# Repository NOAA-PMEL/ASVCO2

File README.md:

# ASVCO2
Open Source Repository for the Autonomous Surface Vehicle CO2 (ASVCO2) gen2 system's firmware and electronics hardware.

## Attribution
You agree to acknowledge NOAA-PMEL and UW on splash pages, and in publications, for products developed with this software.

## UW License
*Refer to the LICENSE file.*

## NOAA Legal Disclaimers
*NOAA does not intend to patent this work worldwide. It may be used freely, but NOAA does not warrant its fitness for any use.*

*As a work of the United States Government, the associated schematics and software are in the public domain within the United States. Additionally, NOAA waives any potential copyright and related rights in the associated schematics and software worldwide.*

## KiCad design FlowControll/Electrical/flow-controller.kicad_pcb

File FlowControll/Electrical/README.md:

# EDD-flow-controller-kicad
KiCad port of ASVCO2 Flow Control board

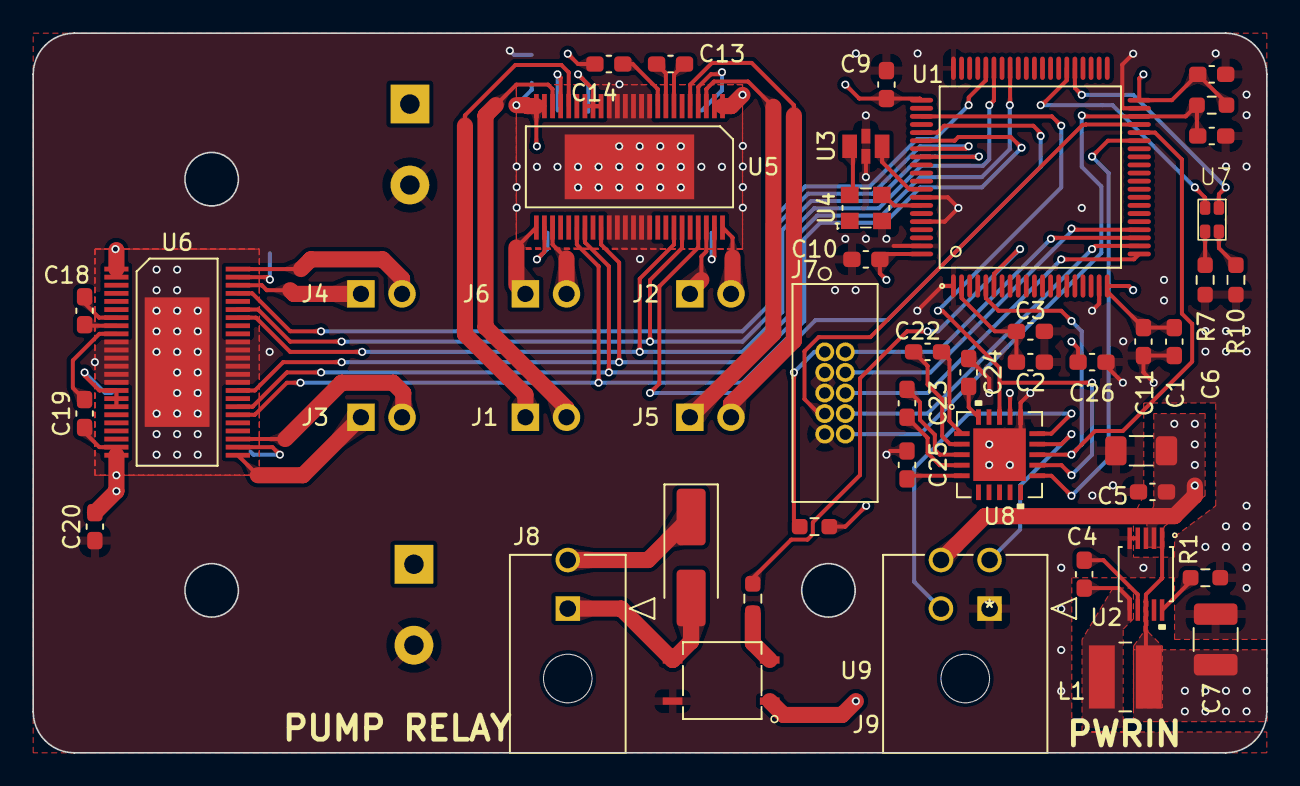
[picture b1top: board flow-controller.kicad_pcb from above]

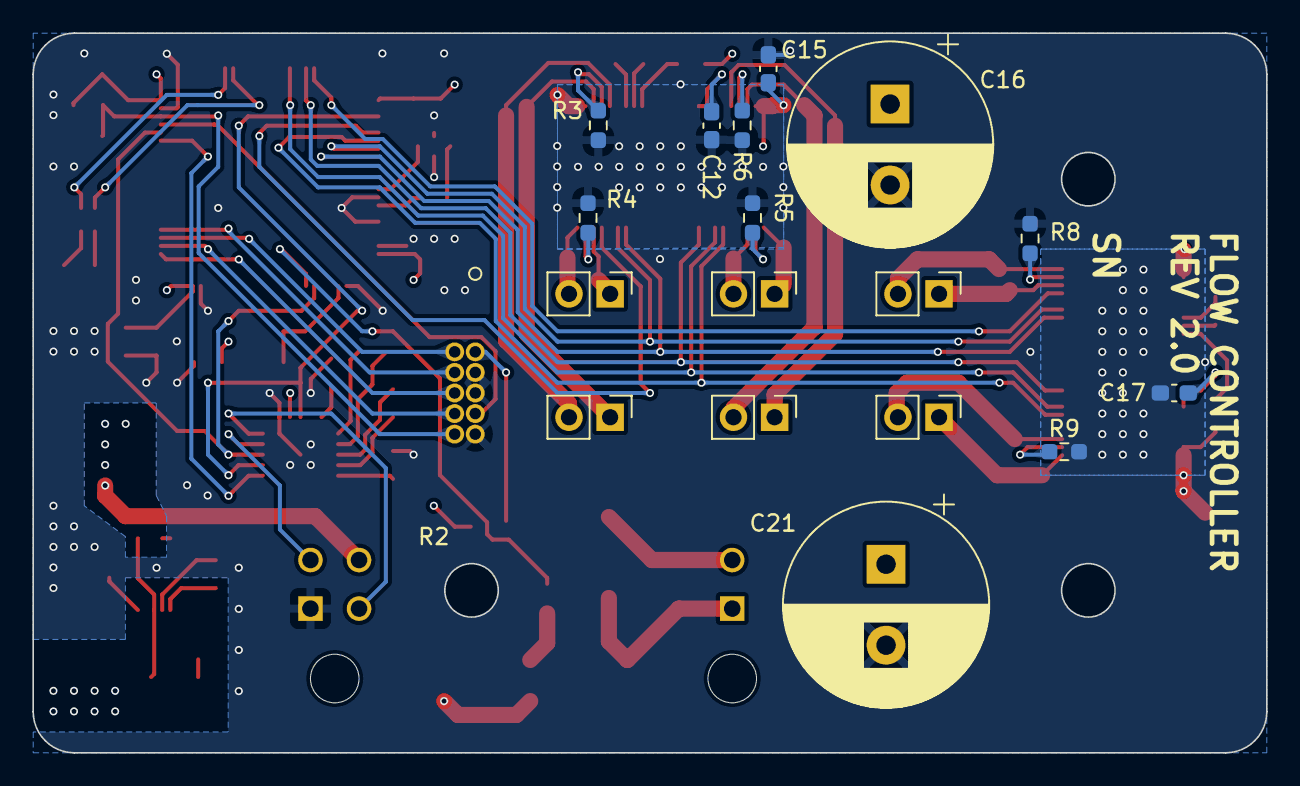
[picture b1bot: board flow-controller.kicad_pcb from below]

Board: 4 copper layers, 76.2 x 44.5 mm, 59 parts (17 on the bottom side), 68 nets.

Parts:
C1, C8, C9, C10: 10uF; C_0603_1608Metric_Pad1.08x0.95mm_HandSolder
C2, C3, C5, C14, C15, C19, C20, C22, C23, C24, C25, C26: 0.1uF; C_0603_1608Metric_Pad1.08x0.95mm_HandSolder
C4: 0.22uF; C_0603_1608Metric_Pad1.08x0.95mm_HandSolder
C6: 10uF; C_1206_3216Metric_Pad1.33x1.80mm_HandSolder
C7: 47uF; C_1210_3225Metric_Pad1.33x2.70mm_HandSolder
C11: 47uF; C_0603_1608Metric_Pad1.08x0.95mm_HandSolder
C12, C17: 0.47uF; C_0603_1608Metric_Pad1.08x0.95mm_HandSolder
C13, C18: 0.01uF; C_0603_1608Metric_Pad1.08x0.95mm_HandSolder
C16, C21: 0.33mF; CP_Radial_D12.5mm_P5.00mm
C27: 10nF; C_0603_1608Metric_Pad1.08x0.95mm_HandSolder
D1: S1B-F-2; D_SMA_Handsoldering
J1: VALVE 1; PinHeader_1x02_P2.54mm_Vertical
J2: VALVE 2; PinHeader_1x02_P2.54mm_Vertical
J3: VALVE 3; PinHeader_1x02_P2.54mm_Vertical
J4: VALVE 4; PinHeader_1x02_P2.54mm_Vertical
J5: VALVE 5; PinHeader_1x02_P2.54mm_Vertical
J6: VALVE 6; PinHeader_1x02_P2.54mm_Vertical
J7: 3220-10-0100-00
J8: PUMP; 430450202
J9: 430450402
L1: VLCF4028T-220MR72-2
R1: 226k; R_0603_1608Metric_Pad0.98x0.95mm_HandSolder
R2: 470R; R_0603_1608Metric_Pad0.98x0.95mm_HandSolder
R3, R4, R5, R6, R8, R9: 0.5; R_0603_1608Metric_Pad0.98x0.95mm_HandSolder
R7, R10: 120; R_0603_1608Metric_Pad0.98x0.95mm_HandSolder
R11: 1k; R_0603_1608Metric_Pad0.98x0.95mm_HandSolder
R12: 47k; R_0603_1608Metric_Pad0.98x0.95mm_HandSolder
U1: MSP430FR5994IPNR
U2: LT3970EMS-3.3-PBF
U3: MEM2012F10R0
U4: SG-210STF 7.3728ML
U5, U6: DRV8823QDCARQ1; HTSSOP48
U7: LTST-C195KGJRKT
U8: MAX3224EETP+
U9: AQY282S

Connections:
+3V3: C1.2, C7.2, C8.2, C9.2, C10.2, C11.2, C26.2, L1.1, R2.1, R12.1, U1.20 (DVCC2), U1.40 (DVCC3), U1.61 (DVCC1), U1.80 (AVCC1), U2.1 (VOUT), U2.8 (BD), U8.17 (VCC), U9.1
+BATT: C5.2, C6.1, C14.1, C15.2, C16.1, C19.1, C20.2, C21.1, D1.1 (K), J8.2, J9.4, U2.2 (EN), U2.3 (VIN), U5.1 (VM1), U5.2 (VM2), U5.23 (VM3), U5.24 (VM4), U6.1 (VM1), U6.2 (VM2), U6.23 (VM3), U6.24 (VM4)
/MCU/A_CS: U1.65 (P5.4_UCA2TXD_UCA2SIMO_TB0OUTH), U5.45 (SCS)
/MCU/B_CS: U1.56 (P5.3_UCB1STE), U6.45 (SCS)
/MCU/JTAG_VCC: J7.1, R2.2
/MCU/ONOFF: U1.63 (P2.3_TA0.0_UCA1STE_A6_C10), U8.12 (FORCEON), U8.18 (~FORCEOFF)
/MCU/P1.1_VREF+: C2.1, C3.1, U1.2 (P1.1_TA0.2_TA1CLK_COUT_A1_C1_VREF+_VERE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)
/MCU/PUMP_RELAY: R11.1, U1.6 (P3.2_A14_C14)
/MCU/R1OUT: U1.5 (P3.1_A13_C13), U1.36 (P2.6_TB0.1_UCA1RXD_UCA1SOMI), U8.13 (R1OUT)
/MCU/RST: C27.1, J7.10, R12.2, U1.38 (RST_NMI_SBWTDIO_N)
/MCU/SBWTCK: J7.7, U1.37 (TEST_SBWTCK)
/MCU/SCLK: U1.55 (P5.2_UCB1CLK_TA4CLK), U5.33 (SCLK), U6.33 (SCLK)
/MCU/SDATA: U1.53 (P5.0_UCB1SIMO_UCB1SDA), U5.31 (SDATA), U6.31 (SDATA)
/MCU/SSTB: U1.66 (P5.5_UCA2RXD_UCA2SOMI_ACLK), U5.30 (SSTB), U6.30 (SSTB)
/MCU/T1IN: U1.35 (P2.5_TB0.0_UCA1TXD_UCA1SIMO), U8.11 (T1IN)
/MCU/TCK: J7.4, U1.24 (PJ.3_TCK_SRCPUOFF_C9)
/MCU/TDI: J7.8, U1.22 (PJ.1_TDI_TCLK_MCLK_SRSCG0_C7)
/MCU/TDO: J7.6, U1.21 (PJ.0_TDO_TB0OUTH_SMCLK_SRSCG1_C6)
/MCU/TMS: J7.2, U1.23 (PJ.2_TMS_ACLK_SROSCOFF_C8)
/MCU/nRESET: U1.67 (P5.6_UCA2CLK_TA4.0_SMCLK), U5.43 (RESETn), U6.43 (RESETn)
/MCU/nSLEEP: U1.68 (P5.7_UCA2STE_TA4.1_MCLK), U5.42 (SLEEPn), U6.42 (SLEEPn)
/Motor Driver 1/AO1: J5.2, U5.5 (AOUT1)
/Motor Driver 1/AO2: J5.1, U5.3 (AOUT2)
/Motor Driver 1/BO1: J2.2, U5.48 (BOUT1)
/Motor Driver 1/BO2: J2.1, U5.46 (BOUT2)
/Motor Driver 1/CO1: J6.2, U5.27 (COUT1)
/Motor Driver 1/CO2: J6.1, U5.25 (COUT2)
/Motor Driver 1/DO1: J1.2, U5.22 (DOUT1)
/Motor Driver 1/DO2: J1.1, U5.20 (DOUT2)
/Motor Driver 1/VREF1: C12.2, U5.16 (V3P3), U5.17 (ABVREF), U5.18 (CDVREF)
/Motor Driver 2/BO1: J4.2, U6.48 (BOUT1)
/Motor Driver 2/BO2: J4.1, U6.46 (BOUT2)
/Motor Driver 2/CO1: J3.2, U6.27 (COUT1)
/Motor Driver 2/CO2: J3.1, U6.25 (COUT2)
/Motor Driver 2/VREF2: C17.2, U6.16 (V3P3), U6.17 (ABVREF), U6.18 (CDVREF)
/RS232 Transceiver/R1IN: J9.3, U8.14 (R1IN)
/RS232 Transceiver/T1OUT: J9.2, U8.15 (T1OUT)
GND: C1.1, C2.2, C3.2, C5.1, C6.2, C7.1, C8.1, C9.1, C10.1, C11.1, C12.1, C15.1, C16.2, C17.1, C20.1, C21.2, C24.2, C25.2, C26.1, C27.2, J7.3, J7.5, J7.9, J9.1, R1.2, R3.2, R4.2, R5.2, R6.2, R7.2, R8.2, R9.2, R10.2, U1.1 (P1.0_TA0.1_DMAE0_RTCCLK_A0_C0_VREF-_VER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), U1.19 (DVSS2), U1.39 (DVSS3), U1.60 (DVSS1), U1.73 (AVSS3), U1.76 (AVSS2), U1.79 (AVSS1), U2.4 (GND), U2.5 (GND), U3.2, U3.4, U4.2 (GND), U5.10 (PGND), U5.11 (PGND), U5.12 (PGND), U5.13 (PGND), U5.14 (PGND), U5.15 (PGND), U5.34 (PGND), U5.35 (PGND), U5.36 (PGND), U5.37 (PGND), U5.38 (PGND), U5.39 (PGND), U5.49 (EPAD), U6.10 (PGND), U6.11 (PGND), U6.12 (PGND), U6.13 (PGND), U6.14 (PGND), U6.15 (PGND), U6.34 (PGND), U6.35 (PGND), U6.36 (PGND), U6.37 (PGND), U6.38 (PGND), U6.39 (PGND), U6.49 (EPAD), U8.16 (GND), U8.21 (EPAD), U9.4
unnamed: D1.2 (A), J8.1, U9.3
unnamed: R7.1, U7.4
unnamed: R10.1, U7.3
unnamed: R11.2, U9.2
unnamed: U1.72 (P6.7_UCB3STE), U3.1
unnamed: U1.45 (P8.2), U7.1
unnamed: U1.46 (P8.3), U7.2
unnamed: U1.74 (PJ.6_HFXIN), U4.3 (OUT)
unnamed: C4.1, U2.7 (BOOST)
unnamed: R1.1, U2.10 (RT)
unnamed: C4.2, L1.2, U2.6 (SW)
unnamed: U3.3, U4.4 (VCC)
unnamed: R3.1, U5.4 (AISEN)
unnamed: R4.1, U5.47 (BISEN)
unnamed: R5.1, U5.26 (CISEN)
unnamed: C13.2, U5.7 (CP1)
unnamed: C13.1, U5.8 (CP2)
unnamed: R6.1, U5.21 (DISEN)
unnamed: C14.2, U5.9 (VCP)
unnamed: R8.1, U6.47 (BISEN)
unnamed: R9.1, U6.26 (CISEN)
unnamed: C18.2, U6.7 (CP1)
unnamed: C18.1, U6.8 (CP2)
unnamed: C19.2, U6.9 (VCP)
unnamed: C22.1, U8.1 (C1+)
unnamed: C22.2, U8.2 (C1-)
unnamed: C23.1, U8.3 (C2+)
unnamed: C23.2, U8.4 (C2-)
unnamed: C24.1, U8.20 (V+)
unnamed: C25.1, U8.5 (V-)

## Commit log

2023-07-27 Adding flow control and pco2 to repo. Legal disclaimers added to README
2025-02-18 update for Kicad files and new firmware
    Also update license files per NOAA and UW requirements.
2025-02-18 Update for new Kicad Schematics and Firmware
2025-02-18 Final update for new KiCAD files
    and proper opensource language
2025-02-18 add BOM and Schematic
2025-02-19 Update LICENSE
2025-02-19 Add pco2sensor BOM and schematics
